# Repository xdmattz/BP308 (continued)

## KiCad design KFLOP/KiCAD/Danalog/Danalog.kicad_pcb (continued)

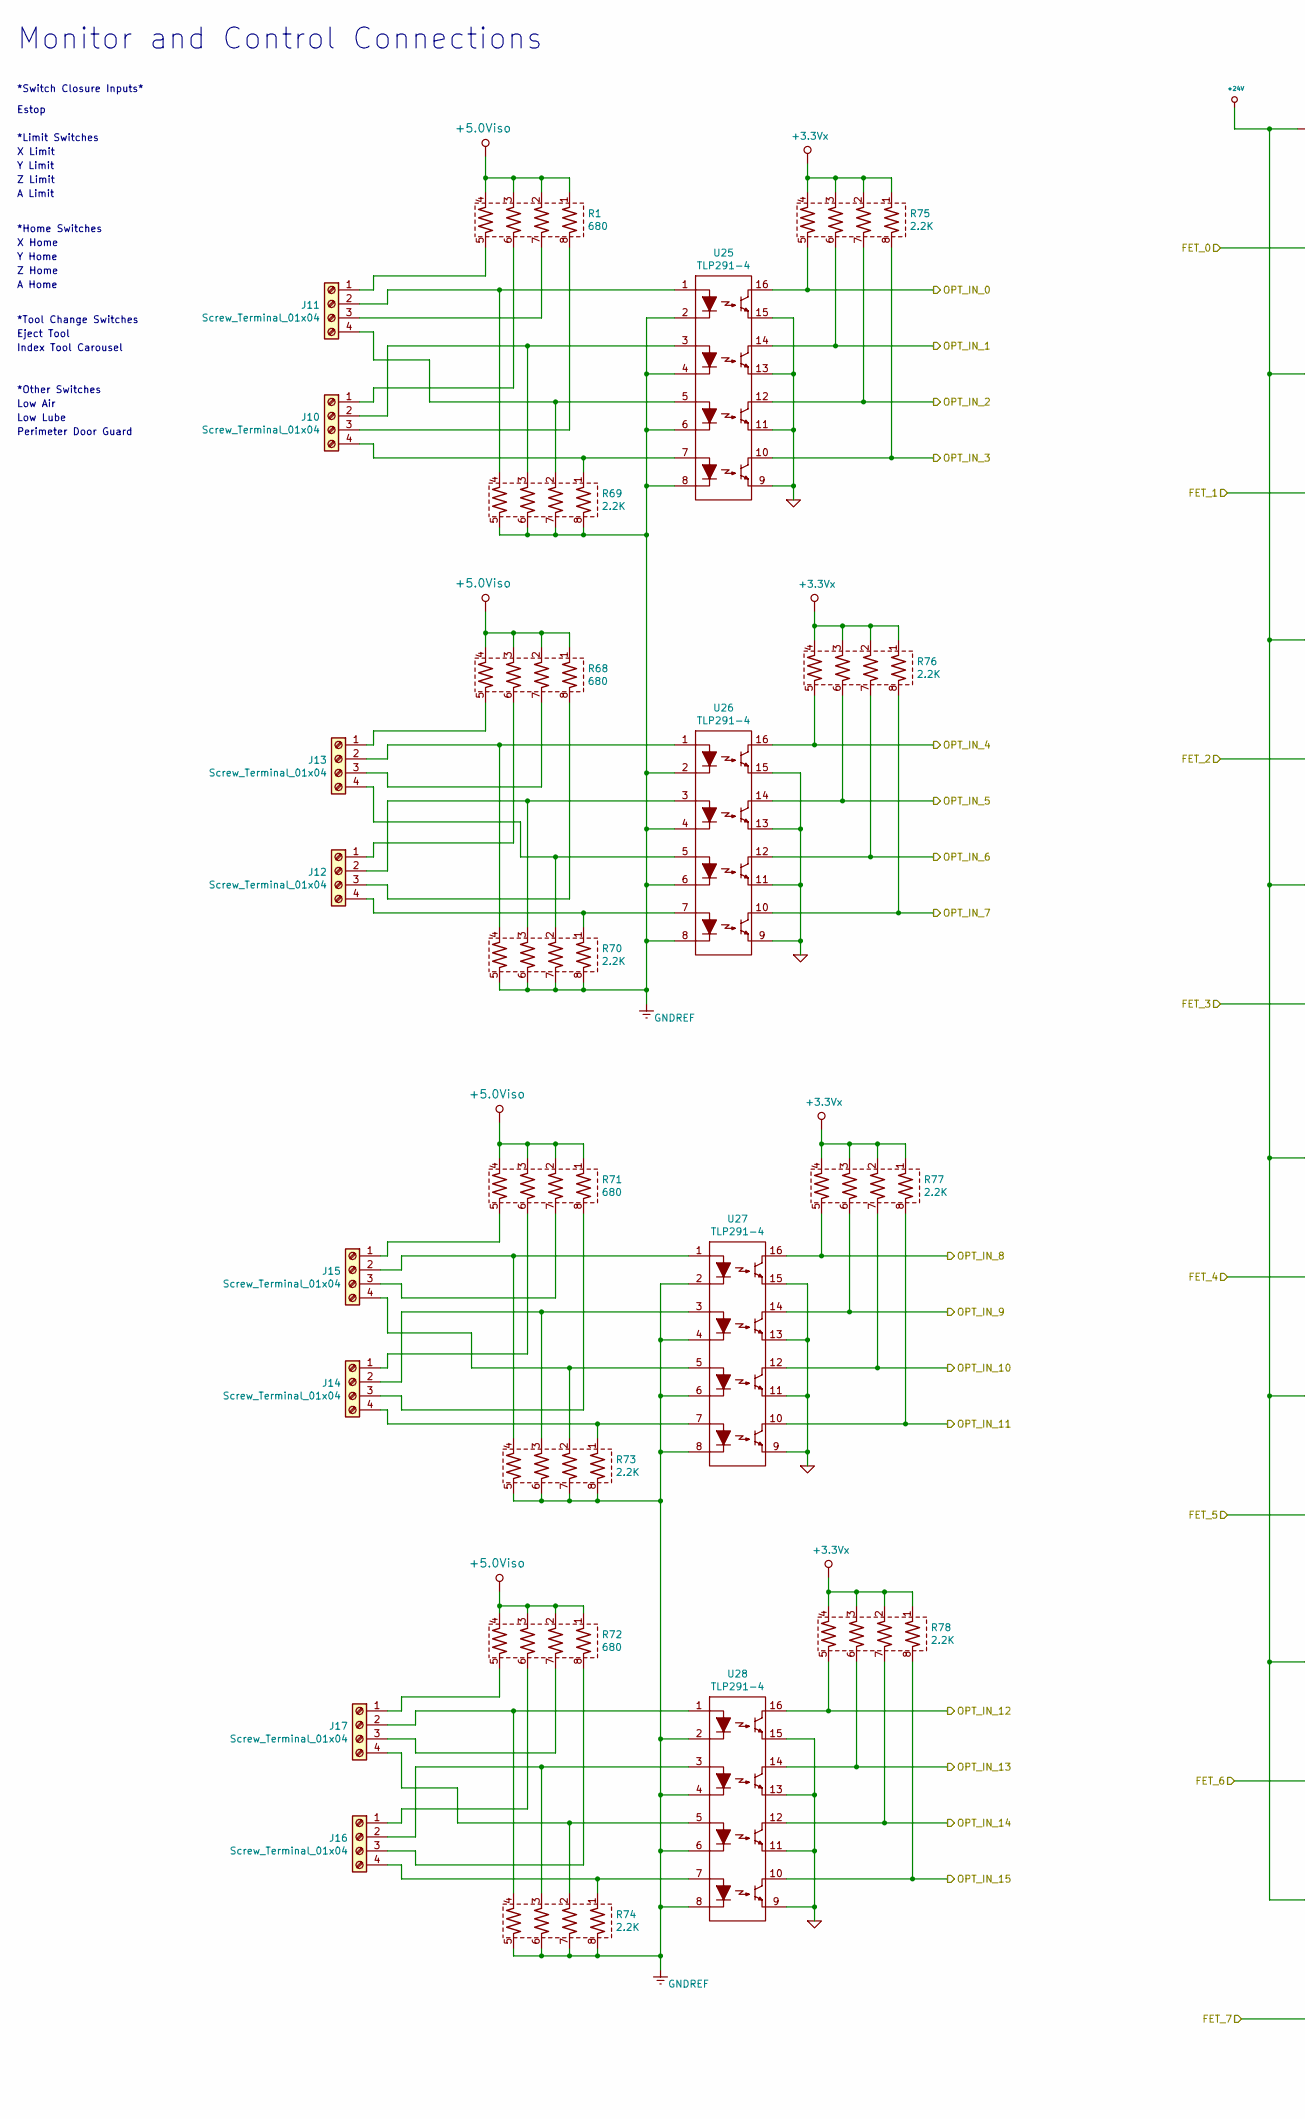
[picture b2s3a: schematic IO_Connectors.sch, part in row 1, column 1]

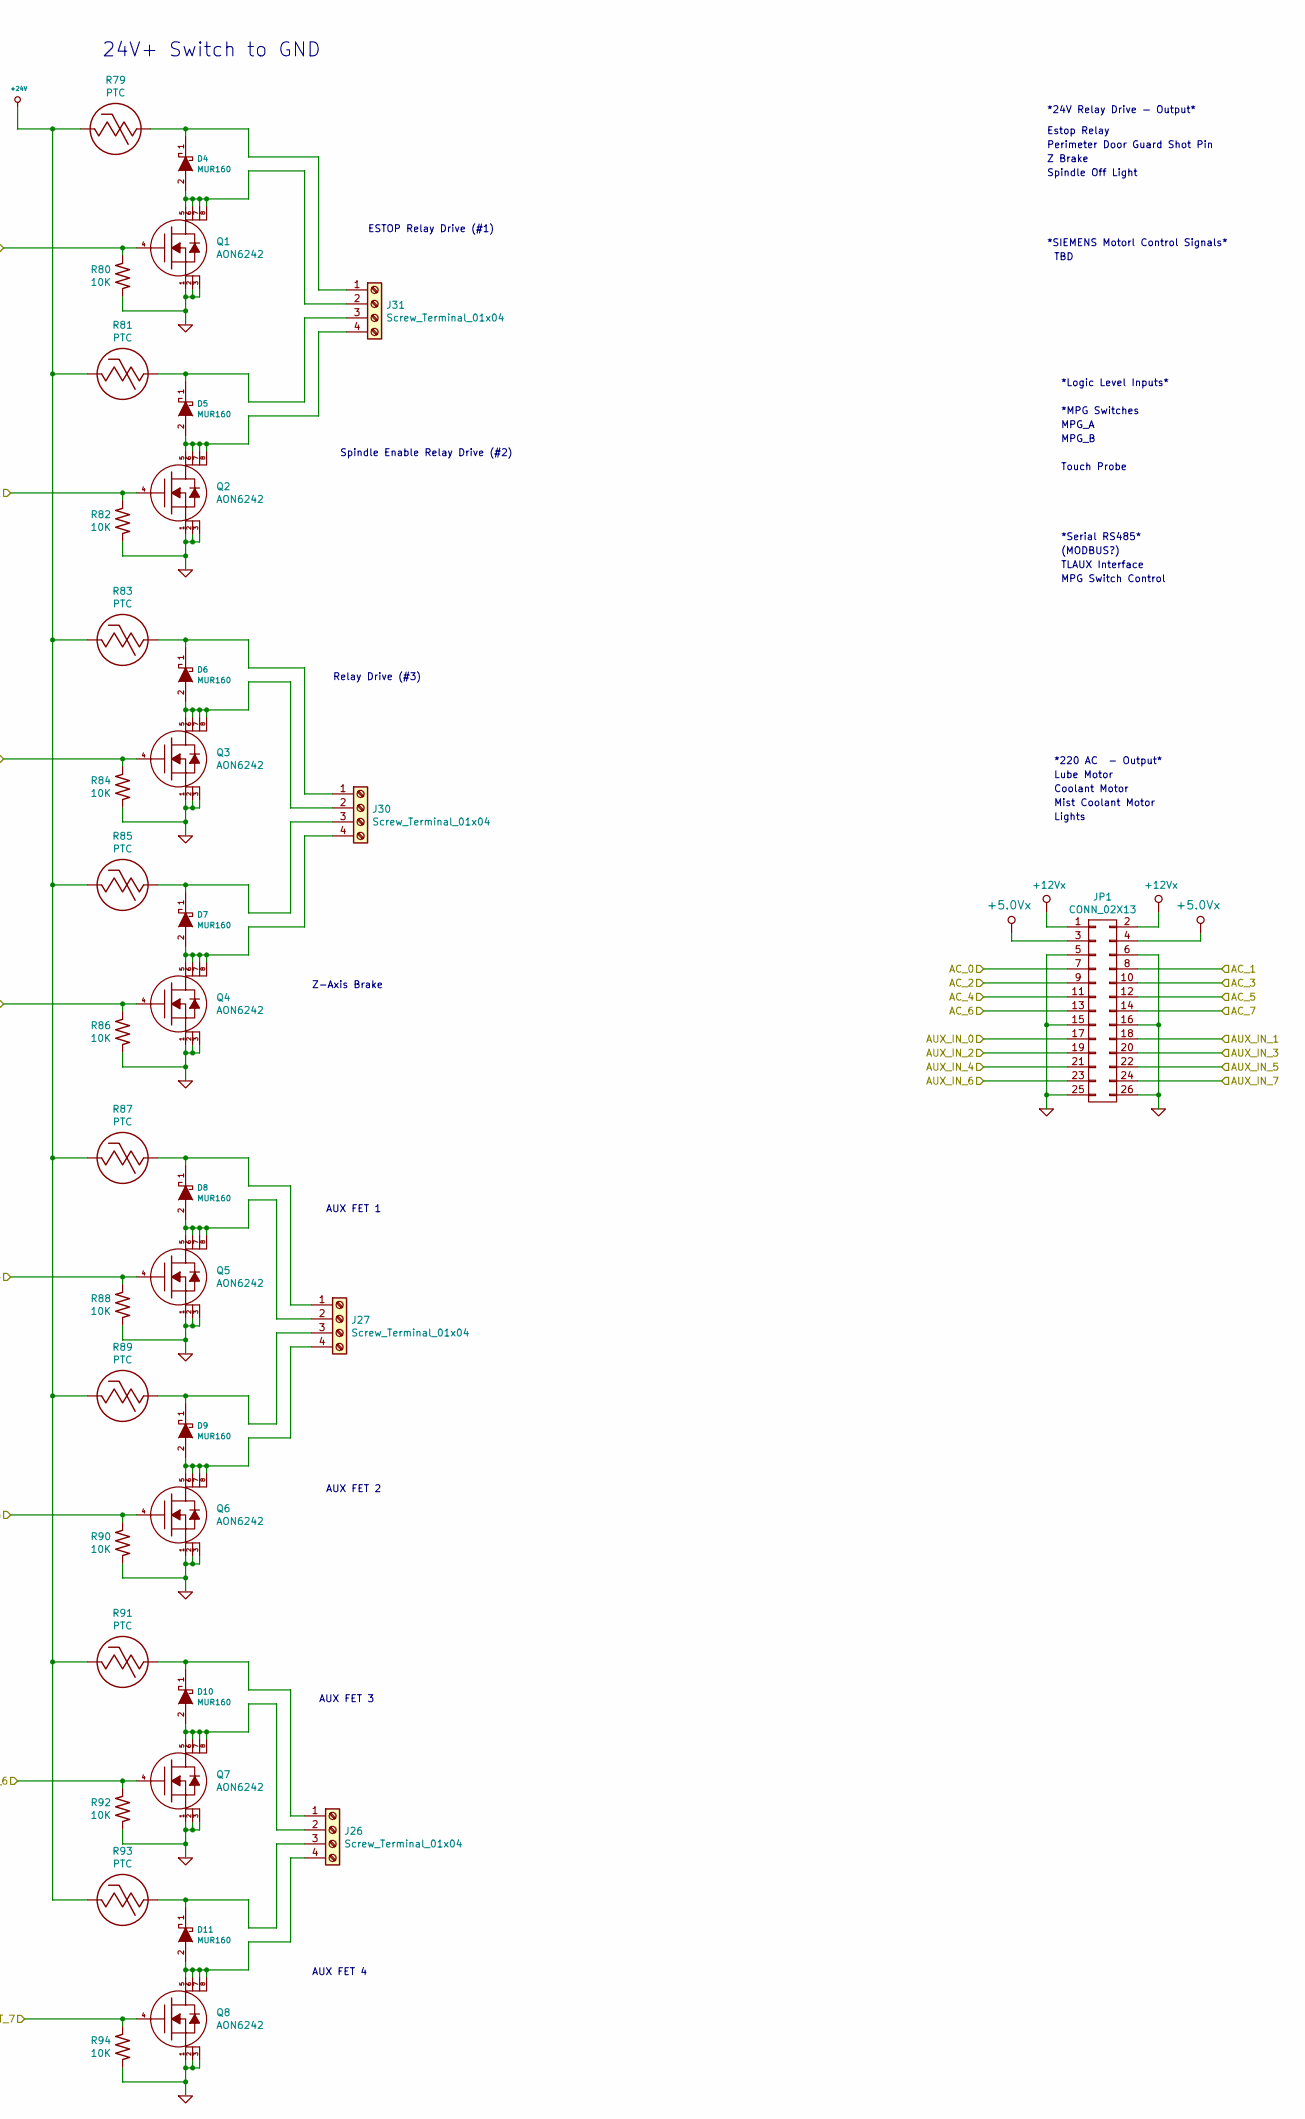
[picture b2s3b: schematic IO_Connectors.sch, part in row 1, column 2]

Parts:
D4, D5, D6, D7, D8, D9, D10, D11: MUR160; DO-214AC
J10, J12, J14, J16, J27, J31: Screw_Terminal_01x04; Terminal_Block_RA_4_5_08mm
J11, J13, J15, J17, J26, J30: Screw_Terminal_01x04; Terminal_Block_Vert_4_5_08mm
JP1: CONN_02X13; vasch_strip_13x2
Q1, Q2, Q3, Q4, Q5, Q6, Q7, Q8: AON6242; psop-8
R1, R68, R71, R72: 680; RES_ARRAY_2012
R69, R70, R73, R74, R75, R76, R77, R78: 2.2K; RES_ARRAY_2012
R79, R81, R83, R85, R87, R89, R91, R93: PTC; OZCF_PTC_7351
R80, R82, R84, R86, R88, R90, R92, R94: 10K; res_0603
U25, U26, U27, U28: TLP291-4; SOIC-16_3.9x9.9mm_Pitch1.27mm

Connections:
+3.3Vx: R75.1, R75.2, R75.3, R75.4, R76.1, R76.2, R76.3, R76.4, R77.1, R77.2, R77.3, R77.4, R78.1, R78.2, R78.3, R78.4; also elsewhere on the board
+5.0Viso: R1.1, R1.2, R1.3, R1.4, R68.1, R68.2, R68.3, R68.4, R71.1, R71.2, R71.3, R71.4, R72.1, R72.2, R72.3, R72.4; also elsewhere on the board
+5.0Vx: JP1.3, JP1.4; also elsewhere on the board
+12Vx: JP1.1, JP1.2; also elsewhere on the board
+24V: R79.2, R81.2, R83.2, R85.2, R87.2, R89.2, R91.2, R93.2; also elsewhere on the board
/AC_0: JP1.7; also elsewhere on the board
/AC_1: JP1.8; also elsewhere on the board
/AC_2: JP1.9; also elsewhere on the board
/AC_3: JP1.10; also elsewhere on the board
/AC_4: JP1.11; also elsewhere on the board
/AC_5: JP1.12; also elsewhere on the board
/AC_6: JP1.13; also elsewhere on the board
/AC_7: JP1.14; also elsewhere on the board
/AUX_IN_0: JP1.17; also elsewhere on the board
/AUX_IN_1: JP1.18; also elsewhere on the board
/AUX_IN_2: JP1.19; also elsewhere on the board
/AUX_IN_3: JP1.20; also elsewhere on the board
/AUX_IN_4: JP1.21; also elsewhere on the board
/AUX_IN_5: JP1.22; also elsewhere on the board
/AUX_IN_6: JP1.23; also elsewhere on the board
/AUX_IN_7: JP1.24; also elsewhere on the board
/FET_0: Q1.4 (G), R80.1; also elsewhere on the board
/FET_1: Q2.4 (G), R82.1; also elsewhere on the board
/FET_2: Q3.4 (G), R84.1; also elsewhere on the board
/FET_3: Q4.4 (G), R86.1; also elsewhere on the board
/FET_4: Q5.4 (G), R88.1; also elsewhere on the board
/FET_5: Q6.4 (G), R90.1; also elsewhere on the board
/FET_6: Q7.4 (G), R92.1; also elsewhere on the board
/FET_7: Q8.4 (G), R94.1; also elsewhere on the board
/OPT_IN_0: R75.5, U25.16 (C1); also elsewhere on the board
/OPT_IN_1: R75.6, U25.14 (C2); also elsewhere on the board
/OPT_IN_2: R75.7, U25.12 (C3); also elsewhere on the board
/OPT_IN_3: R75.8, U25.10 (C4); also elsewhere on the board
/OPT_IN_4: R76.5, U26.16 (C1); also elsewhere on the board
/OPT_IN_5: R76.6, U26.14 (C2); also elsewhere on the board
/OPT_IN_6: R76.7, U26.12 (C3); also elsewhere on the board
/OPT_IN_7: R76.8, U26.10 (C4); also elsewhere on the board
/OPT_IN_8: R77.5, U27.16 (C1); also elsewhere on the board
/OPT_IN_9: R77.6, U27.14 (C2); also elsewhere on the board
/OPT_IN_10: R77.7, U27.12 (C3); also elsewhere on the board
/OPT_IN_11: R77.8, U27.10 (C4); also elsewhere on the board
/OPT_IN_12: R78.5, U28.16 (C1); also elsewhere on the board
/OPT_IN_13: R78.6, U28.14 (C2); also elsewhere on the board
/OPT_IN_14: R78.7, U28.12 (C3); also elsewhere on the board
/OPT_IN_15: R78.8, U28.10 (C4); also elsewhere on the board
GND: JP1.5, JP1.6, JP1.15, JP1.16, JP1.25, JP1.26, Q1.1 (S), Q1.2 (S), Q1.3 (S), Q2.1 (S), Q2.2 (S), Q2.3 (S), Q3.1 (S), Q3.2 (S), Q3.3 (S), Q4.1 (S), Q4.2 (S), Q4.3 (S), Q5.1 (S), Q5.2 (S), Q5.3 (S), Q6.1 (S), Q6.2 (S), Q6.3 (S), Q7.1 (S), Q7.2 (S), Q7.3 (S), Q8.1 (S), Q8.2 (S), Q8.3 (S), R80.2, R82.2, R84.2, R86.2, R88.2, R90.2, R92.2, R94.2, U25.9 (E4), U25.11 (E3), U25.13 (E2), U25.15 (E1), U26.9 (E4), U26.11 (E3), U26.13 (E2), U26.15 (E1), U27.9 (E4), U27.11 (E3), U27.13 (E2), U27.15 (E1), U28.9 (E4), U28.11 (E3), U28.13 (E2), U28.15 (E1); also elsewhere on the board
GNDREF: R69.5, R69.6, R69.7, R69.8, R70.5, R70.6, R70.7, R70.8, R73.5, R73.6, R73.7, R73.8, R74.5, R74.6, R74.7, R74.8, U25.2 (K1), U25.4 (K2), U25.6 (K3), U25.8 (K4), U26.2 (K1), U26.4 (K2), U26.6 (K3), U26.8 (K4), U27.2 (K1), U27.4 (K2), U27.6 (K3), U27.8 (K4), U28.2 (K1), U28.4 (K2), U28.6 (K3), U28.8 (K4); also elsewhere on the board
unnamed: D4.1 (K), J31.1, R79.1
unnamed: D4.2 (A), J31.2, Q1.5 (D), Q1.6 (D), Q1.7 (D), Q1.8 (D)
unnamed: D5.1 (K), J31.3, R81.1
unnamed: D5.2 (A), J31.4, Q2.5 (D), Q2.6 (D), Q2.7 (D), Q2.8 (D)
unnamed: D6.1 (K), J30.1, R83.1
unnamed: D6.2 (A), J30.2, Q3.5 (D), Q3.6 (D), Q3.7 (D), Q3.8 (D)
unnamed: D7.1 (K), J30.3, R85.1
unnamed: D7.2 (A), J30.4, Q4.5 (D), Q4.6 (D), Q4.7 (D), Q4.8 (D)
unnamed: D8.1 (K), J27.1, R87.1
unnamed: D8.2 (A), J27.2, Q5.5 (D), Q5.6 (D), Q5.7 (D), Q5.8 (D)
unnamed: D9.1 (K), J27.3, R89.1
unnamed: D9.2 (A), J27.4, Q6.5 (D), Q6.6 (D), Q6.7 (D), Q6.8 (D)
unnamed: D10.1 (K), J26.1, R91.1
unnamed: D10.2 (A), J26.2, Q7.5 (D), Q7.6 (D), Q7.7 (D), Q7.8 (D)
unnamed: D11.1 (K), J26.3, R93.1
unnamed: D11.2 (A), J26.4, Q8.5 (D), Q8.6 (D), Q8.7 (D), Q8.8 (D)
unnamed: J10.1, R1.6
unnamed: J10.2, R69.3, U25.3 (A2)
unnamed: J10.3, R1.8
unnamed: J10.4, R69.1, U25.7 (A4)
unnamed: J11.1, R1.5
unnamed: J11.2, R69.4, U25.1 (A1)
unnamed: J11.3, R1.7
unnamed: J11.4, R69.2, U25.5 (A3)
unnamed: J12.1, R68.6
unnamed: J12.2, R70.3, U26.3 (A2)
unnamed: J12.3, R68.8
unnamed: J12.4, R70.1, U26.7 (A4)
unnamed: J13.1, R68.5
unnamed: J13.2, R70.4, U26.1 (A1)
unnamed: J13.3, R68.7
unnamed: J13.4, R70.2, U26.5 (A3)
unnamed: J14.1, R71.6
unnamed: J14.2, R73.3, U27.3 (A2)
unnamed: J14.3, R71.8
unnamed: J14.4, R73.1, U27.7 (A4)
unnamed: J15.1, R71.5
unnamed: J15.2, R73.4, U27.1 (A1)
unnamed: J15.3, R71.7
unnamed: J15.4, R73.2, U27.5 (A3)
unnamed: J16.1, R72.6
unnamed: J16.2, R74.3, U28.3 (A2)
unnamed: J16.3, R72.8
unnamed: J16.4, R74.1, U28.7 (A4)
unnamed: J17.1, R72.5
unnamed: J17.2, R74.4, U28.1 (A1)
unnamed: J17.3, R72.7
unnamed: J17.4, R74.2, U28.5 (A3)

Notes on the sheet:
Monitor and Control Connections
*Switch Closure Inputs*
Estop
*Limit Switches
X Limit
Y Limit
Z Limit
A Limit
X Home
*Home Switches
Y Home
Z Home
A Home
*Tool Change Switches
Eject Tool
Index Tool Carousel
*Other Switches
Low Air
Low Lube
Perimeter Door Guard
*24V Relay Drive - Output*
Estop Relay
Perimeter Door Guard Shot Pin
Z Brake
Spindle Off Light
Touch Probe
*220 AC - Output*
Lube Motor
Coolant Motor
Mist Coolant Motor
Lights
*MPG Switches
MPG_A
MPG_B
*Logic Level Inputs*
*Serial RS485*
TLAUX Interface
MPG Switch Control
(MODBUS?)
*SIEMENS Motorl Control Signals*

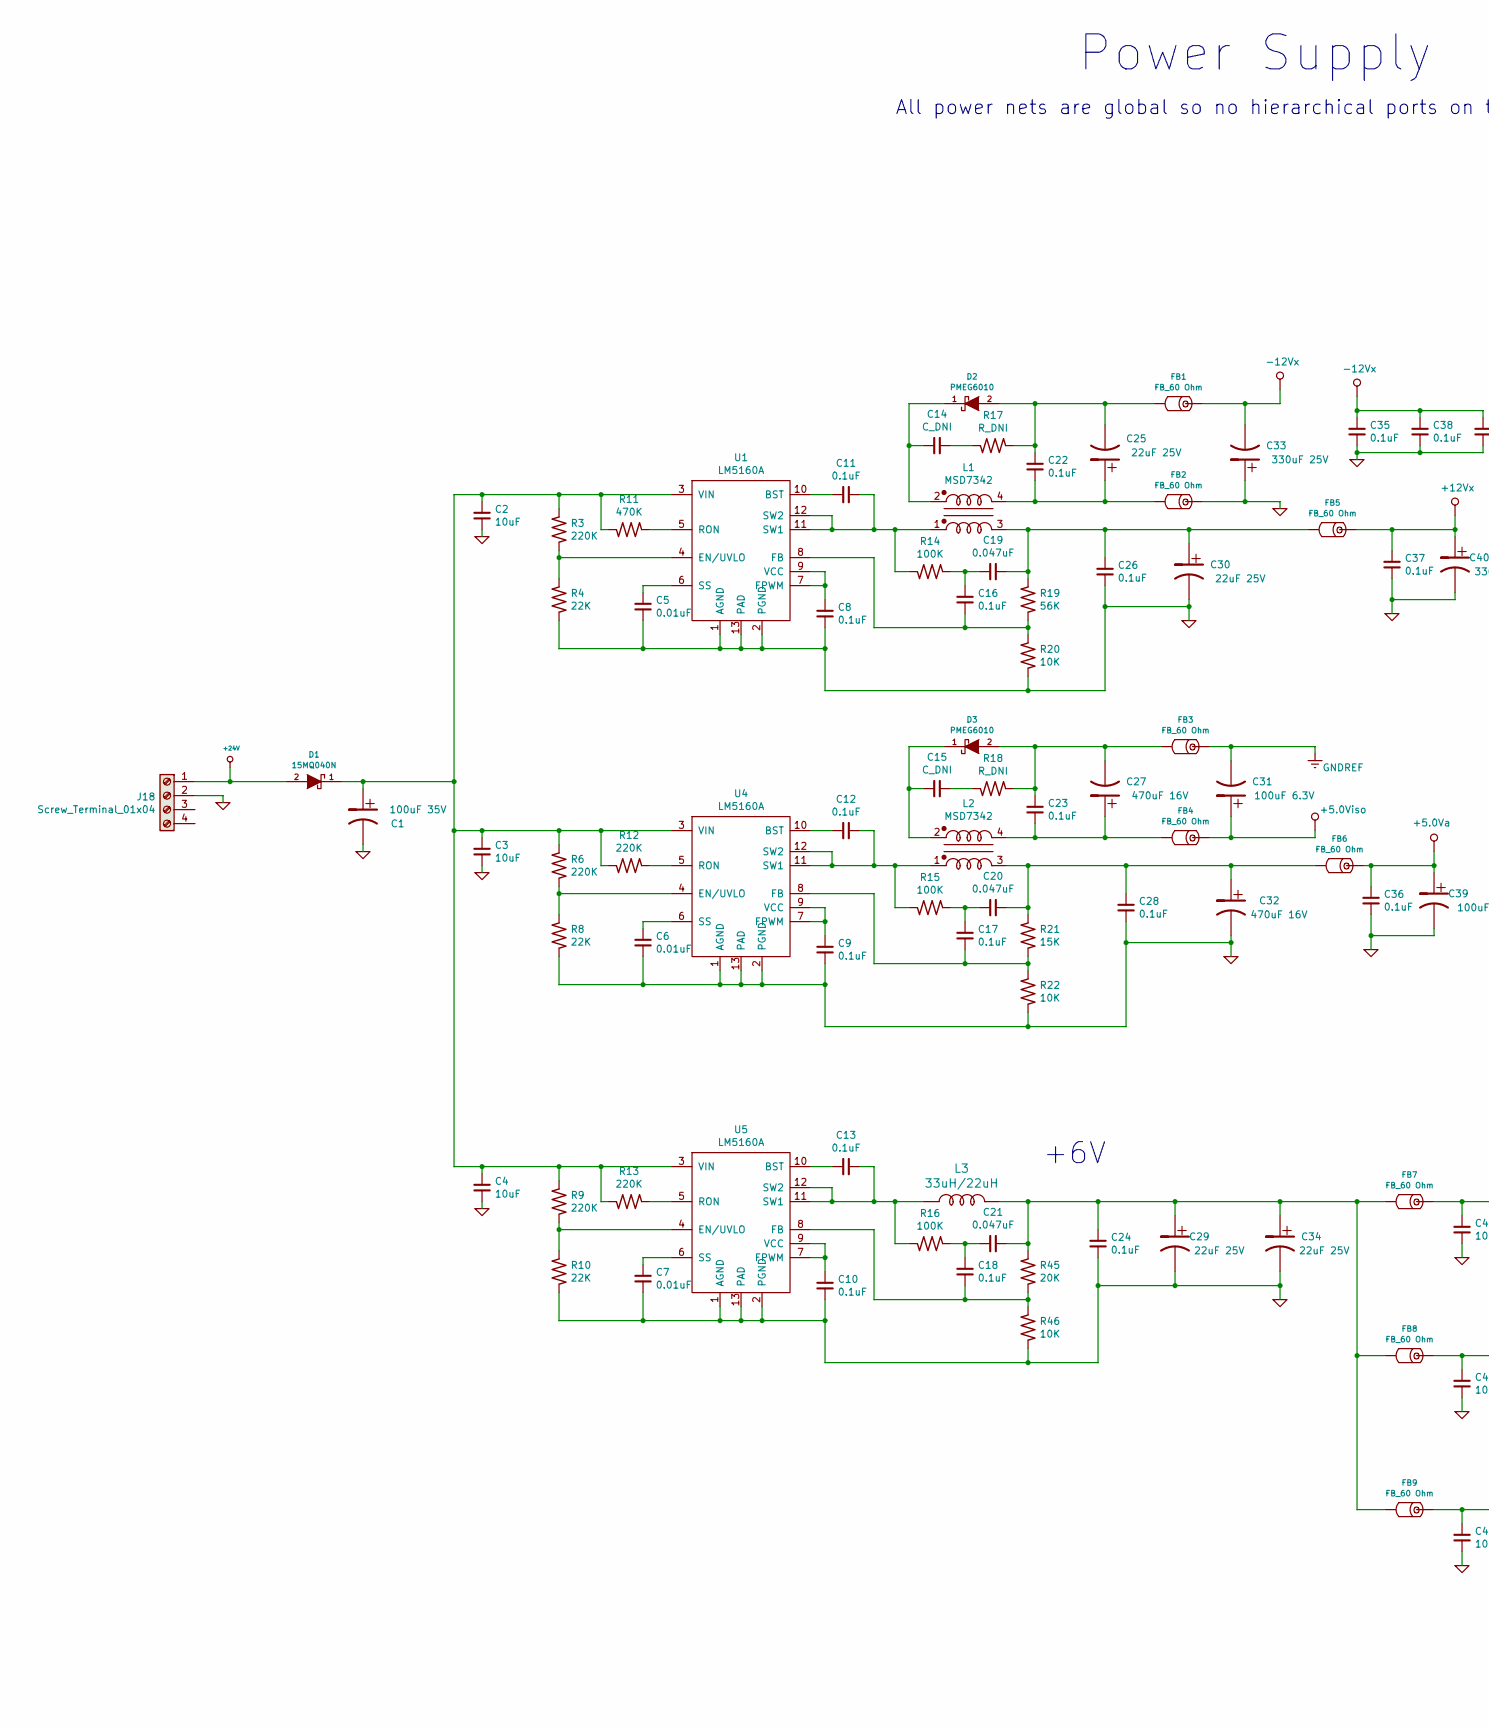
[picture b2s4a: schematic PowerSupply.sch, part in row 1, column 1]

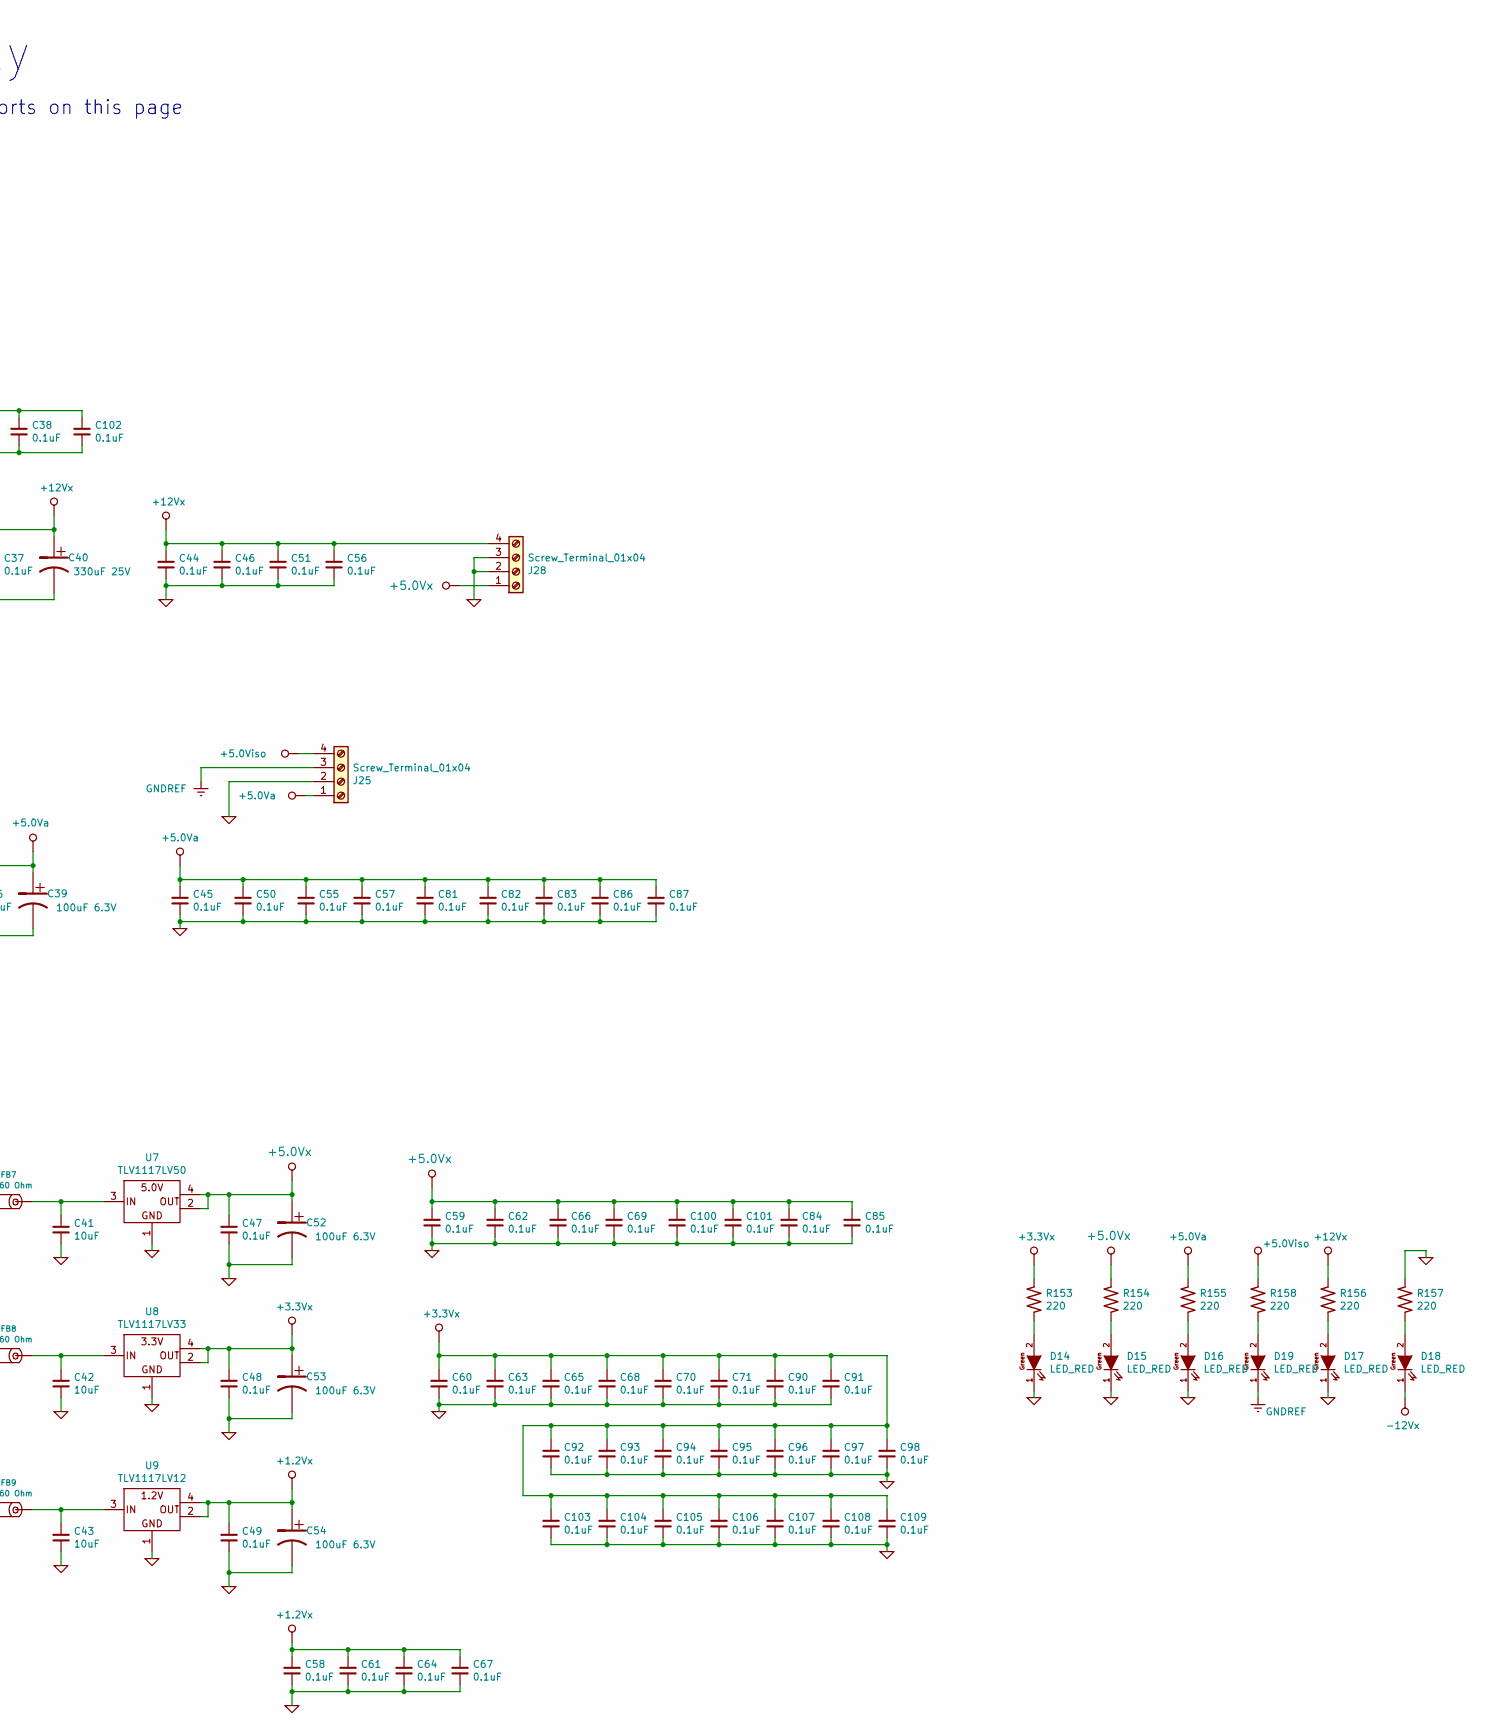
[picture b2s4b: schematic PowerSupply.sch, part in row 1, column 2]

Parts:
C1: 100uF 35V; CP_Elec_10x10
C2, C3, C4: 10uF; cap_1210
C5, C6, C7: 0.01uF; cap_0603
C8, C9, C10, C11, C12, C13, C16, C17, C18, C22, C23, C24, C26, C28, C35, C36, C37, C38, C44, C45, C46, C47, C48, C49, C50, C51, C55, C56, C57, C58, C59, C60, C61, C62, C63, C64, C65, C66, C67, C68, C69, C70, C71, C81, C82, C83, C84, C85, C86, C87, C90, C91, C92, C93, C94, C95, C96, C97, C98, C100, C101, C102, C103, C104, C105, C106, C107, C108, C109: 0.1uF; cap_0603
C14, C15: C_DNI; cap_0603
C19, C20, C21: 0.047uF; cap_0603
C25, C29, C30, C34: 22uF 25V; Tan_Cap_B
C27, C32: 470uF 16V; CP_Elec_8x10
C31, C39, C52, C53, C54: 100uF 6.3V; Tan_Cap_B
C33, C40: 330uF 25V; CP_Elec_8x10
C41, C42, C43: 10uF; cap_0805
D1: 15MQ040N; DO-214AC
D2, D3: PMEG6010; SOD-123
D14, D15, D16, D17, D18, D19: LED_RED; Led_1206_Short
FB1, FB2, FB3, FB4, FB5, FB6, FB7, FB8, FB9: FB_60 Ohm; fb_0805
J18, J25, J28: Screw_Terminal_01x04; Terminal_Block_RA_4_5_08mm
L1, L2: MSD7342
L3: 33uH/22uH; XAL7070
R3, R6, R9, R12, R13: 220K; res_0603
R4, R8, R10: 22K; res_0603
R11: 470K; res_0603
R14, R15, R16: 100K; res_0603
R17, R18: R_DNI; res_0805
R19: 56K; res_0603
R20, R22, R46: 10K; res_0603
R21: 15K; res_0603
R45: 20K; res_0603
R153, R154, R155, R156, R157, R158: 220; res_0603
U1, U4, U5: LM5160A; WSON-12
U7: TLV1117LV50; SOT-223
U8: TLV1117LV33; SOT-223
U9: TLV1117LV12; SOT-223

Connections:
+1.2Vx: C49.2, C54.1, C58.2, C61.2, C64.2, C67.2, U9.2 (OUT), U9.4 (OUT); also elsewhere on the board
+3.3Vx: C48.2, C53.1, C60.2, C63.2, C65.2, C68.2, C70.2, C71.2, C90.2, C91.2, C92.2, C93.2, C94.2, C95.2, C96.2, C97.2, C98.2, C103.2, C104.2, C105.2, C106.2, C107.2, C108.2, C109.2, R153.2, U8.2 (OUT), U8.4 (OUT); also elsewhere on the board
+5.0Va: C36.2, C39.1, C45.2, C50.2, C55.2, C57.2, C81.2, C82.2, C83.2, C86.2, C87.2, FB6.1, J25.1, R155.2; also elsewhere on the board
+5.0Viso: C31.1, FB4.1, J25.4, R158.2; also elsewhere on the board
+5.0Vx: C47.2, C52.1, C59.2, C62.2, C66.2, C69.2, C84.2, C85.2, C100.2, C101.2, J28.1, R154.2, U7.2 (OUT), U7.4 (OUT); also elsewhere on the board
+12Vx: C37.2, C40.1, C44.2, C46.2, C51.2, C56.2, FB5.1, J28.4, R156.2; also elsewhere on the board
+24V: D1.2 (A), J18.1; also elsewhere on the board
-12Vx: C33.2, C35.2, C38.2, C102.2, D18.1 (K), FB1.1; also elsewhere on the board
GND: C1.2, C2.1, C3.1, C4.1, C5.2, C6.2, C7.2, C8.2, C9.2, C10.2, C24.2, C26.2, C28.2, C29.2, C30.2, C32.2, C33.1, C34.2, C35.1, C36.1, C37.1, C38.1, C39.2, C40.2, C41.1, C42.1, C43.1, C44.1, C45.1, C46.1, C47.1, C48.1, C49.1, C50.1, C51.1, C52.2, C53.2, C54.2, C55.1, C56.1, C57.1, C58.1, C59.1, C60.1, C61.1, C62.1, C63.1, C64.1, C65.1, C66.1, C67.1, C68.1, C69.1, C70.1, C71.1, C81.1, C82.1, C83.1, C84.1, C85.1, C86.1, C87.1, C90.1, C91.1, C92.1, C93.1, C94.1, C95.1, C96.1, C97.1, C98.1, C100.1, C101.1, C102.1, C103.1, C104.1, C105.1, C106.1, C107.1, C108.1, C109.1, D14.1 (K), D15.1 (K), D16.1 (K), D17.1 (K), FB2.1, J18.2, J25.2, J28.2, J28.3, R4.1, R8.1, R10.1, R20.2, R22.2, R46.2, R157.2, U1.1 (AGND), U1.2 (PGND), U1.13 (PAD), U4.1 (AGND), U4.2 (PGND), U4.13 (PAD), U5.1 (AGND), U5.2 (PGND), U5.13 (PAD), U7.1 (GND), U8.1 (GND), U9.1 (GND); also elsewhere on the board
GNDREF: C31.2, D19.1 (K), FB3.1, J25.3; also elsewhere on the board
unnamed: C1.1, C2.2, C3.2, C4.2, D1.1 (K), R3.2, R6.2, R9.2, R11.2, R12.2, R13.2, U1.3 (VIN), U4.3 (VIN), U5.3 (VIN)
unnamed: C5.1, U1.6 (SS)
unnamed: C6.1, U4.6 (SS)
unnamed: C7.1, U5.6 (SS)
unnamed: C8.1, U1.7 (FPWM), U1.9 (VCC)
unnamed: C9.1, U4.7 (FPWM), U4.9 (VCC)
unnamed: C10.1, U5.7 (FPWM), U5.9 (VCC)
unnamed: C11.1, L1.1, R14.2, U1.11 (SW1), U1.12 (SW2)
unnamed: C11.2, U1.10 (BST)
unnamed: C12.1, L2.1, R15.2, U4.11 (SW1), U4.12 (SW2)
unnamed: C12.2, U4.10 (BST)
unnamed: C13.1, L3.1, R16.2, U5.11 (SW1), U5.12 (SW2)
unnamed: C13.2, U5.10 (BST)
unnamed: C14.1, R17.2
unnamed: C14.2, D2.1 (K), L1.2
unnamed: C15.1, R18.2
unnamed: C15.2, D3.1 (K), L2.2
unnamed: C16.1, C19.2, R14.1
unnamed: C16.2, R19.2, R20.1, U1.8 (FB)
unnamed: C17.1, C20.2, R15.1
unnamed: C17.2, R21.2, R22.1, U4.8 (FB)
unnamed: C18.1, C21.2, R16.1
unnamed: C18.2, R45.2, R46.1, U5.8 (FB)
unnamed: C19.1, C26.1, C30.1, FB5.2, L1.3, R19.1
unnamed: C20.1, C28.1, C32.1, FB6.2, L2.3, R21.1
unnamed: C21.1, C24.1, C29.1, C34.1, FB7.2, FB8.2, FB9.2, L3.2, R45.1
unnamed: C22.1, C25.2, D2.2 (A), FB1.2, R17.1
unnamed: C22.2, C25.1, FB2.2, L1.4
unnamed: C23.1, C27.2, D3.2 (A), FB3.2, R18.1
unnamed: C23.2, C27.1, FB4.2, L2.4
unnamed: C41.2, FB7.1, U7.3 (IN)
unnamed: C42.2, FB8.1, U8.3 (IN)
unnamed: C43.2, FB9.1, U9.3 (IN)
unnamed: D14.2 (A), R153.1
unnamed: D15.2 (A), R154.1
unnamed: D16.2 (A), R155.1
unnamed: D17.2 (A), R156.1
unnamed: D18.2 (A), R157.1
unnamed: D19.2 (A), R158.1
unnamed: R3.1, R4.2, U1.4 (EN/UVLO)
unnamed: R6.1, R8.2, U4.4 (EN/UVLO)
unnamed: R9.1, R10.2, U5.4 (EN/UVLO)
unnamed: R11.1, U1.5 (RON)
unnamed: R12.1, U4.5 (RON)
unnamed: R13.1, U5.5 (RON)

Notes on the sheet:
Power Supply
All power nets are global so no hierarchical ports on this page
+6V
